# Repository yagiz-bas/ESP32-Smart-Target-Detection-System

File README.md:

# ESP32 Smart Target Detection System

A compact ESP32-based target detection and alarm system using an HC-SR04 ultrasonic sensor, an SG90 servo, an SSD1306 OLED display, a buzzer, and a red LED.

The system continuously scans its surroundings by rotating the ultrasonic sensor with a servo. When an object enters the configured detection range, the system confirms the detection, locks the servo at the detected angle, activates visual and audible alarms, and displays the target distance and angle on the OLED. When the target disappears, the alarm is cleared and scanning resumes from the position where the target was lost.

## Features

* Servo-based horizontal scanning from 30° to 150°
* HC-SR04 ultrasonic distance measurement
* Three consecutive detections required for target confirmation
* Target lock at the detected servo angle
* Real-time distance and angle display on a 0.96" SSD1306 OLED
* Red LED visual alarm
* Passive buzzer audible alarm
* Three consecutive lost readings required before unlocking
* Automatic scan recovery after target disappearance
* ESP32-based embedded control
* KiCad schematic and PCB design
* ERC-verified schematic
* DRC-verified PCB layout
* Gerber and drill files included

## How It Works

### 1. Scanning

The SG90 servo rotates the HC-SR04 across the configured scan range.

The OLED displays the current:

* Distance
* Servo angle
* System state

Example:

```text
SCANNING

Distance: 82.4 cm
Angle: 72 deg
```

### 2. Target Detection

When the measured distance drops below the detection threshold, the system does not immediately trigger the alarm.

The target must be detected for **three consecutive measurements**.

This reduces false triggering caused by individual noisy readings.

### 3. Target Lock

After three consecutive detections:

* The servo stops at the detected angle.
* The red LED turns on.
* The buzzer activates.
* The OLED switches to `TARGET LOCKED`.
* The measured distance and servo angle are displayed.

Example:

```text
TARGET
LOCKED

DIST: 24.7 cm
ANGLE: 117 deg
```

### 4. Target Lost

While locked, the system continues measuring the target distance.

If the target remains beyond the loss threshold for **three consecutive measurements**:

* The buzzer stops.
* The red LED turns off.
* The lock state is cleared.
* Scanning resumes from the previous servo position.

The system therefore operates continuously:

```text
SCAN
  ↓
TARGET DETECTED
  ↓
TARGET LOCKED
  ↓
ALARM
  ↓
TARGET LOST
  ↓
RESUME SCAN
```

## Hardware

| Component          | Function                           |
| ------------------ | ---------------------------------- |
| ESP32-WROOM-32     | Main microcontroller               |
| HC-SR04            | Ultrasonic distance measurement    |
| SG90 Servo         | Rotates the ultrasonic sensor      |
| 0.96" SSD1306 OLED | Displays state, distance and angle |
| Red LED            | Visual alarm indicator             |
| 1 kΩ Resistor      | LED current limiting               |
| Passive Buzzer     | Audible alarm                      |

## Pinout

| Component    | ESP32 GPIO |
| ------------ | ---------: |
| HC-SR04 TRIG |     GPIO 5 |
| HC-SR04 ECHO |     GPIO 4 |
| SG90 Signal  |    GPIO 18 |
| OLED SDA     |    GPIO 21 |
| OLED SCL     |    GPIO 22 |
| Buzzer       |    GPIO 25 |
| Red LED      |    GPIO 26 |

### Power

* OLED → 3.3 V
* HC-SR04 → 5 V
* SG90 → 5 V
* Buzzer → GPIO 25 / GND
* LED → GPIO 26 → 1 kΩ → LED → GND

> **Hardware note:** The HC-SR04 ECHO output can exceed the ESP32's 3.3 V GPIO logic level. A proper voltage divider or level-shifting stage is recommended for a production-ready version.

## Software

The firmware was developed using the Arduino framework for ESP32.

### Libraries

```text
ESP32Servo
Adafruit GFX Library
Adafruit SSD1306
Wire
```

## Project Structure

```text
ESP32-Smart-Target-Detection-System/
│
├── Firmware/
│   └── Target Lock Radar System.ino
│
├── Hardware/
│   ├── ESP32_Radar_System.kicad_pro
│   ├── ESP32_Radar_System.kicad_sch
│   └── ESP32_Radar_System.kicad_pcb
│
├── Images/
│   ├── schematic.png
│   ├── pcb-layout.png
│   └── pcb-3d.png
│
├── Media/
│   └── media.gif
│
├── gerbers/
│   ├── ESP32_Radar_System-F_Cu.gbr
│   ├── ESP32_Radar_System-B_Cu.gbr
│   ├── ESP32_Radar_System-F_Mask.gbr
│   ├── ESP32_Radar_System-B_Mask.gbr
│   ├── ESP32_Radar_System-F_Paste.gbr
│   ├── ESP32_Radar_System-B_Paste.gbr
│   ├── ESP32_Radar_System-F_Silkscreen.gbr
│   ├── ESP32_Radar_System-B_Silkscreen.gbr
│   ├── ESP32_Radar_System-Edge_Cuts.gbr
│   ├── ESP32_Radar_System-PTH.drl
│   ├── ESP32_Radar_System-NPTH.drl
│   └── ESP32_Radar_System-job.gbrjob
│
├── LICENSE
└── README.md
```

## PCB Design

The PCB was designed in KiCad using a complete schematic-to-PCB workflow:

1. Schematic design
2. ERC verification
3. Footprint assignment
4. Component placement
5. PCB routing
6. GND copper zone
7. DRC verification
8. Gerber generation
9. Drill file generation

### Schematic

### PCB Layout

### 3D PCB View

## Detection Parameters

Current firmware parameters:

```text
Scan range:              30° – 150°
Detection threshold:     35 cm
Target loss threshold:   45 cm
Detection confirmation:  3 consecutive readings
Loss confirmation:       3 consecutive readings
Scan step:               3°
```

These parameters can be modified directly in the Arduino firmware.

## Getting Started

### Hardware

Connect the components according to the KiCad schematic:

```text
Hardware/ESP32_Radar_System.kicad_sch
```

### Firmware

Open the Arduino sketch from:

```text
Firmware/Target Lock Radar System.ino
```

Install the required libraries, select the appropriate ESP32 board, and upload the firmware.

### OLED

The firmware uses an SSD1306 I²C OLED with the default I²C address:

```text
0x3C
```

After startup, the system begins scanning automatically.

## Gerber Files

Production Gerber and drill files generated from the KiCad PCB are available in:

```text
gerbers/
```

The folder contains the required copper, solder-mask, silkscreen, board-outline, and drilling data for PCB fabrication.

## Design Notes

This project uses a **single-axis ultrasonic scanning architecture**.

The HC-SR04 measures distance along the direction in which it is currently pointing. The system performs target detection and angular lock, but it does **not** perform camera-based object classification or continuous visual tracking.

The project was built to demonstrate practical embedded-system concepts including:

* GPIO control
* Ultrasonic distance measurement
* Servo control
* I²C communication
* OLED interfacing
* Event detection
* State-machine logic
* Alarm control
* PCB schematic design
* PCB routing
* ERC and DRC verification
* Gerber generation

## Future Improvements

Possible extensions include:

* Two-axis pan/tilt scanning
* Camera-based object tracking
* PC-based real-time visualization
* Wireless telemetry
* Event logging
* Distance history graphs
* Additional sensing technologies
* Proper HC-SR04 ECHO level shifting
* Improved power distribution

## License

This project is released under the MIT License.

See [`LICENSE`](LICENSE) for the full license text.

## Author

Developed as an ESP32 embedded-systems and PCB-design project.

---

**ESP32 + HC-SR04 + SG90 + SSD1306 + Buzzer + LED**

A compact prototype for ultrasonic target detection, angular locking, visual indication, audible alarm, and automatic scan recovery.

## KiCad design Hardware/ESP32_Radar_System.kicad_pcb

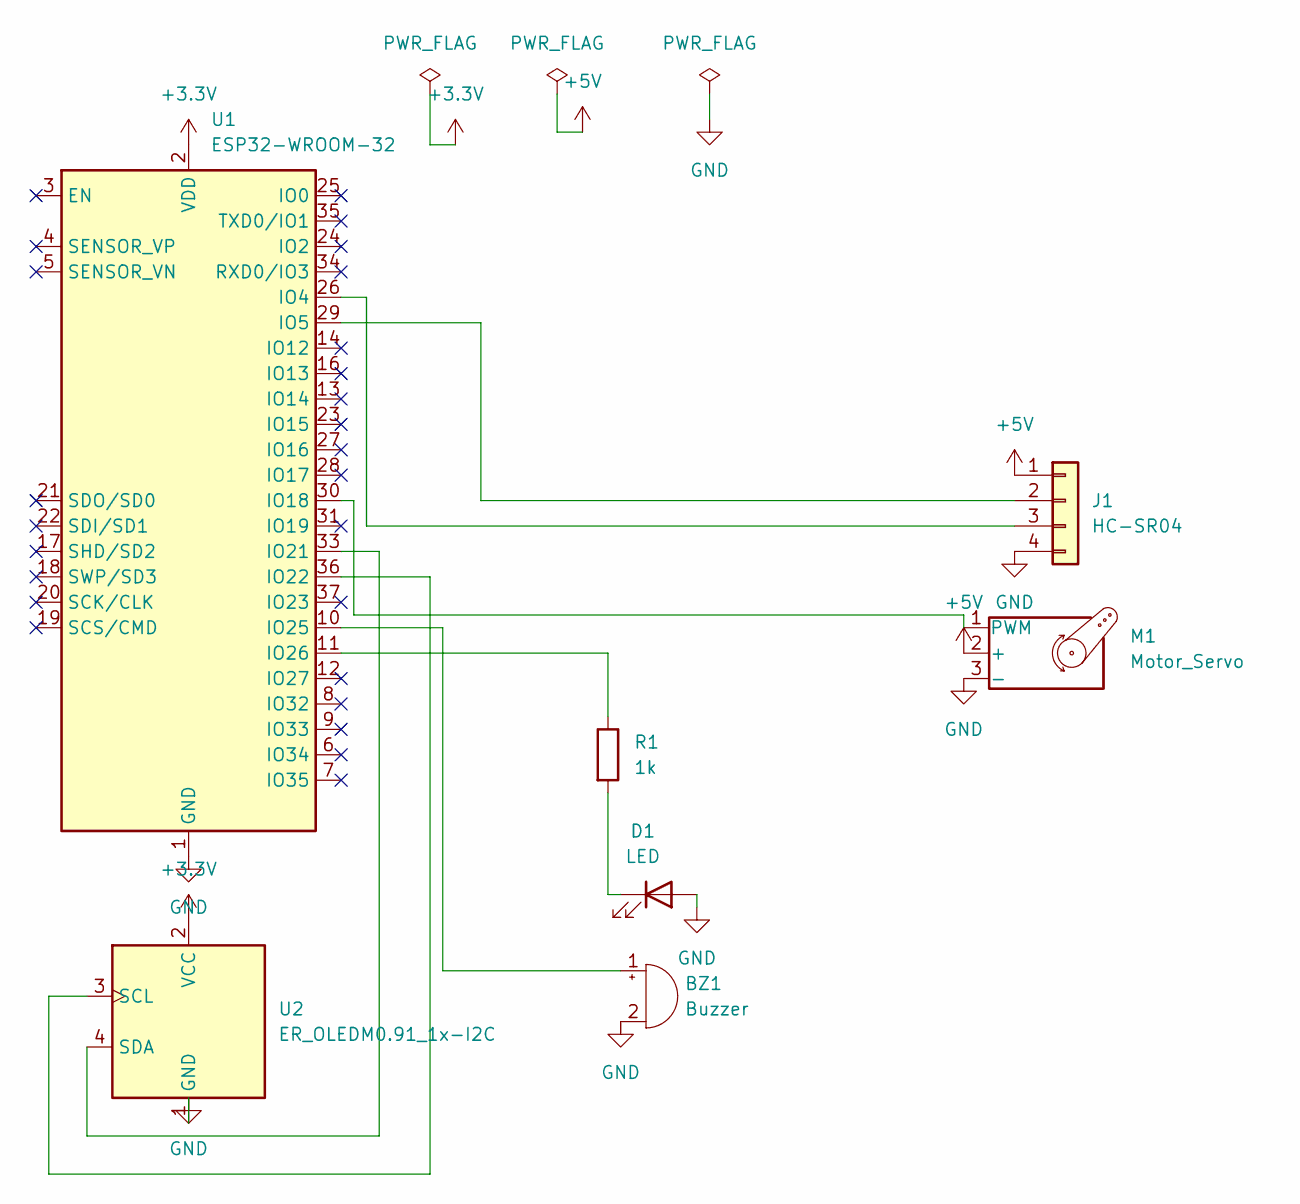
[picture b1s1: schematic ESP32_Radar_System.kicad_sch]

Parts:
BZ1: Buzzer; PinHeader_1x02_P2.54mm_Vertical
D1: LED; LED_D5.0mm
J1: HC-SR04; PinHeader_1x04_P2.54mm_Vertical
M1: Motor_Servo; PinHeader_1x04_P2.54mm_Vertical
R1: 1k; R_Axial_DIN0207_L6.3mm_D2.5mm_P10.16mm_Horizontal
U1: ESP32-WROOM-32
U2: ER_OLEDM0.91_1x-I2C; PinHeader_1x04_P2.54mm_Vertical

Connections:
+3.3V: U1.2 (VDD), U2.2 (VCC)
+5V: J1.1, M1.2 (+)
GND: BZ1.2 (-), D1.2 (A), J1.4, M1.3 (-), U1.1 (GND), U1.15 (GND), U1.38 (GND), U1.39 (GND), U2.1 (GND)
unnamed: BZ1.1 (+), U1.10 (IO25)
unnamed: D1.1 (K), R1.2
unnamed: J1.2, U1.29 (IO5)
unnamed: J1.3, U1.26 (IO4)
unnamed: M1.1 (PWM), U1.30 (IO18)
unnamed: U1.33 (IO21), U2.4 (SDA)
unnamed: U1.36 (IO22), U2.3 (SCL)
unnamed: R1.1, U1.11 (IO26)

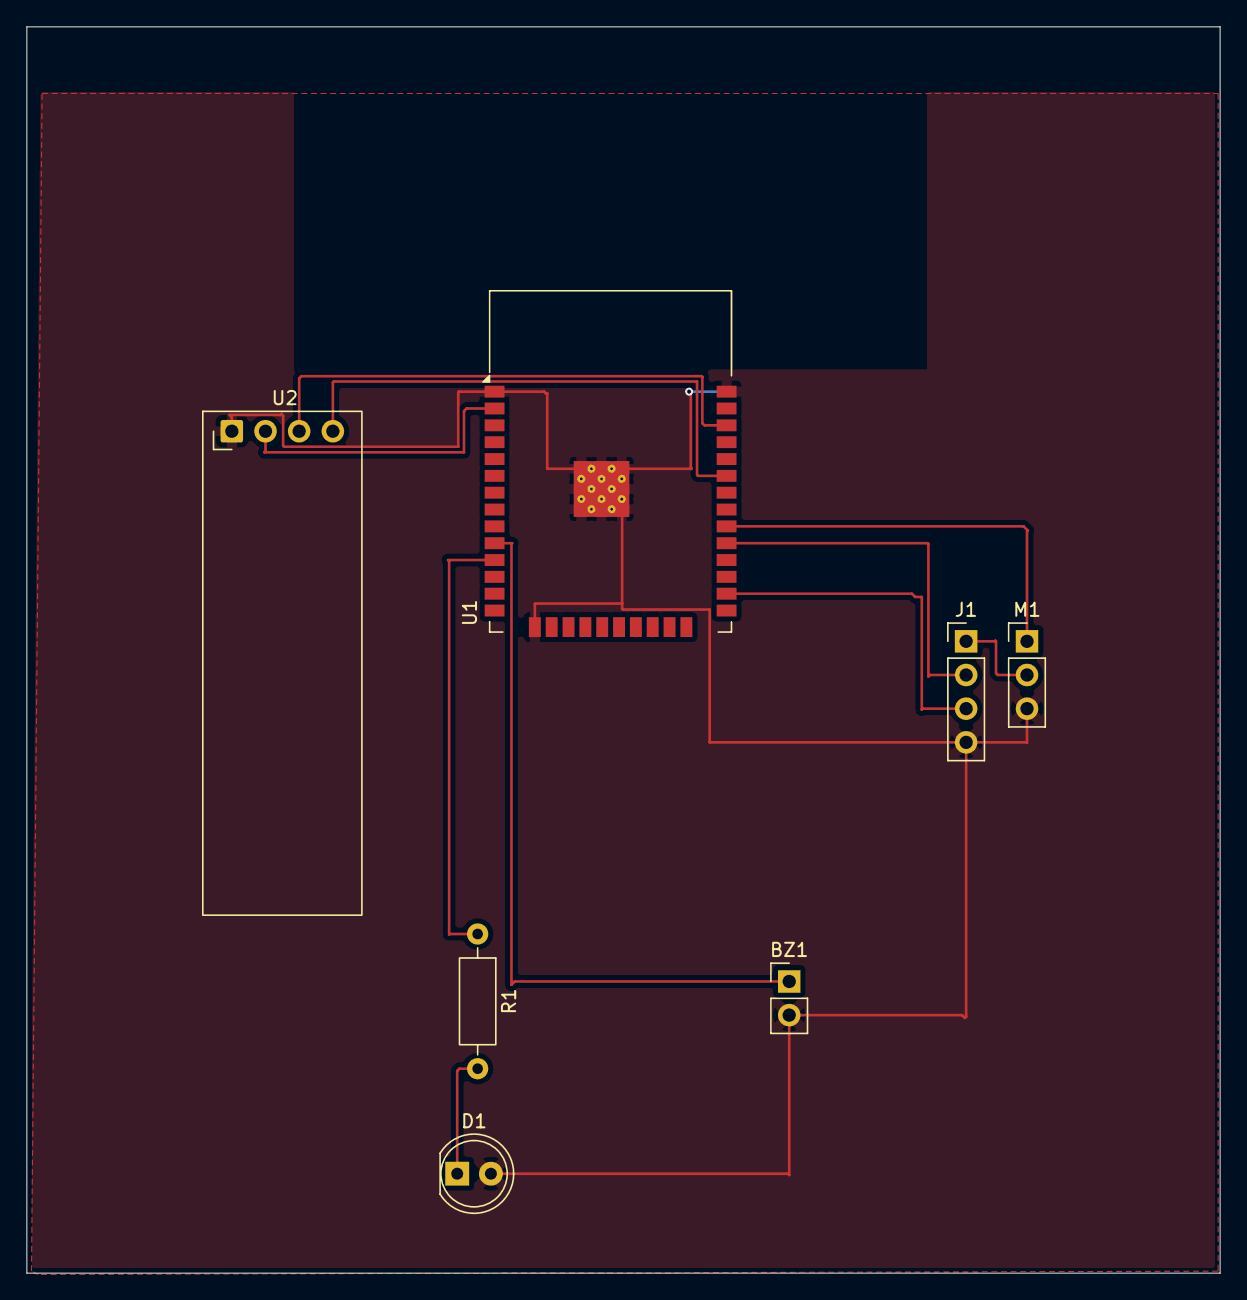
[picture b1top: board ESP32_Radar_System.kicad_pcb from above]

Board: 2 copper layers, 90.0 x 94.0 mm, 7 parts (0 on the bottom side), 11 nets.
